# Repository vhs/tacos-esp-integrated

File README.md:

# TACOS ESP integrated

This is the integrated interlock and terminal TACOS reference implementation on ESP/embedded (Platform IO).

## TACOS

[TACOS](https://github.com/vhs/tacos/) is an integrated tool access control operations system.

## Usage

* Clone this repository: `git clone https://github.com/vhs/tacos-esp-integrated`
* Copy includes/config.sample.h to includes/config.h
  * Configure NODE_ID
  * Enable and/or disable LOCKOUT and/or AUTH_TERMINAL functionality
  * Configure wifi, NODE_SECRET, backend, NTP, IO and default settings as needed
    * NODE_SECRET is only needed for authentication
* Copy `platformio.sample.ini` to `platformio.ini`
* Configure boards as needed
* Compile and upload

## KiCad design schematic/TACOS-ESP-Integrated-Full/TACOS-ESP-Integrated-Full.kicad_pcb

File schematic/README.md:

# Schematics

## TACOS-ESP-Integrated-Full

This is a schematic for the full TACOS-ESP-Integrated design, which includes arming and NFC functionality.

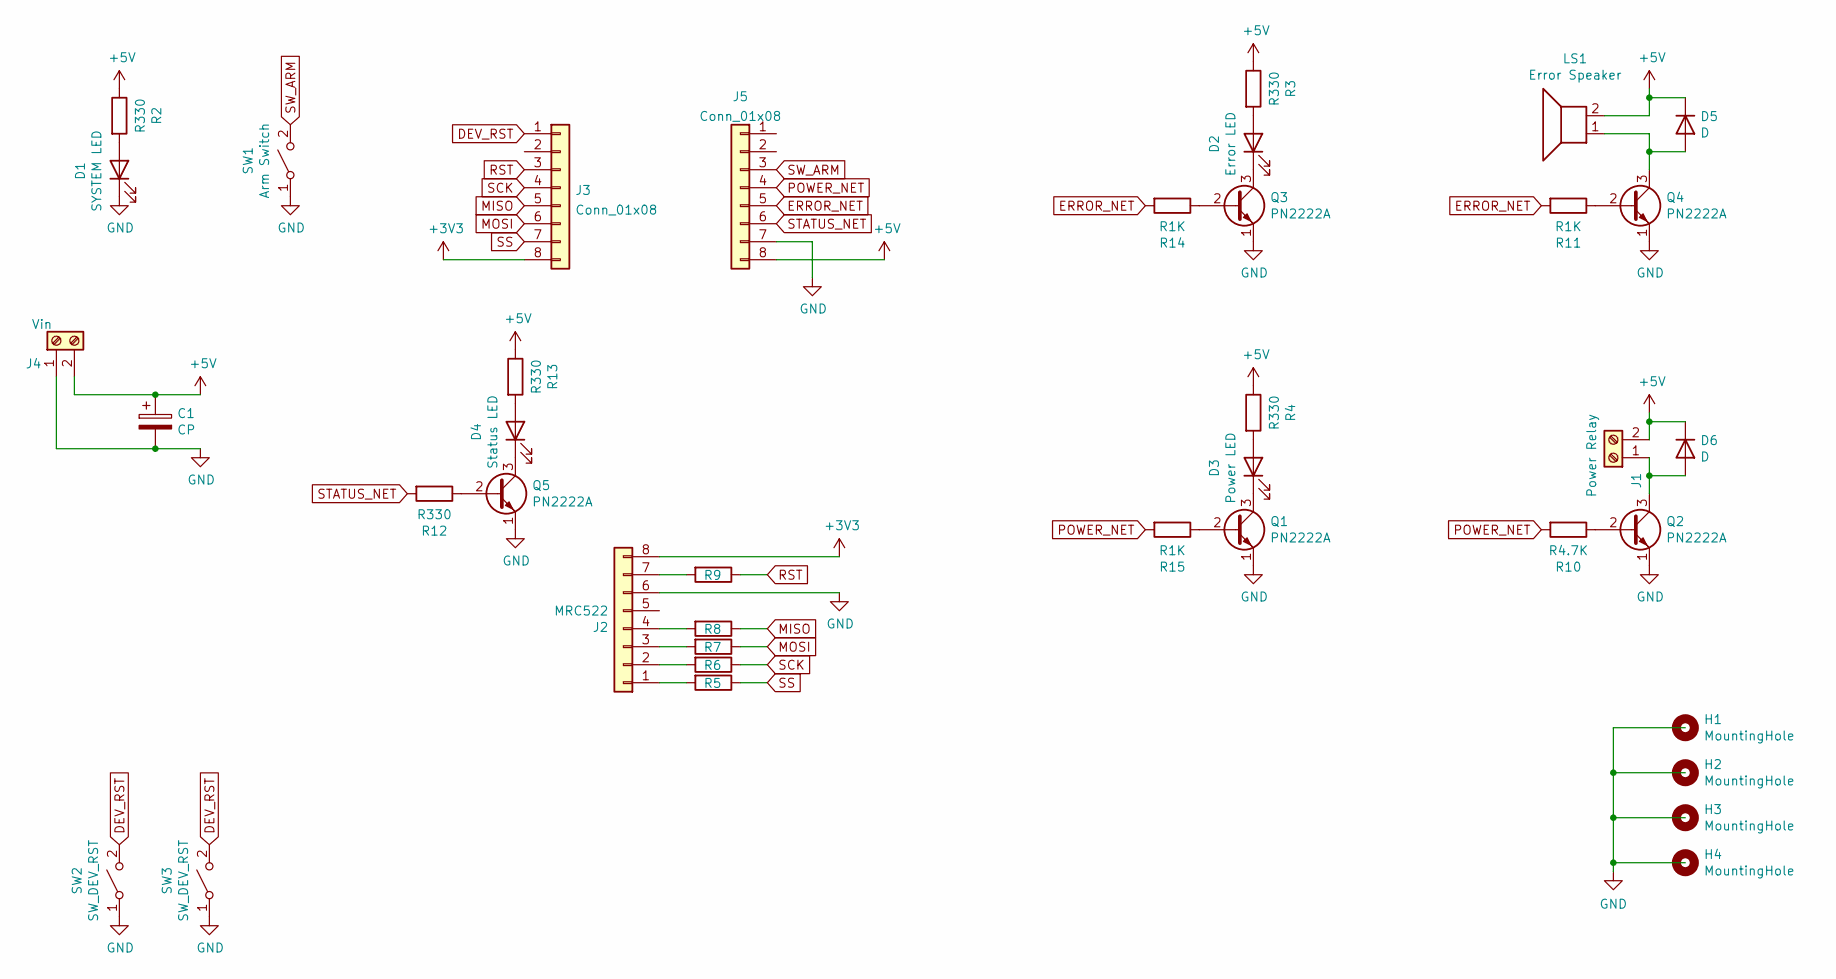
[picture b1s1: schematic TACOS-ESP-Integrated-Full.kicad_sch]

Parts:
C1: CP; CP_Radial_D5.0mm_P2.50mm
D1: SYSTEM LED; TerminalBlock_bornier-2_P5.08mm
D2: Error LED; TerminalBlock_bornier-2_P5.08mm
D3: Power LED; TerminalBlock_bornier-2_P5.08mm
D4: Status LED; TerminalBlock_bornier-2_P5.08mm
D5, D6: D; D_0603_1608Metric
H1, H2, H3, H4: MountingHole; MountingHole_3.2mm_M3_Pad
J1: Power Relay; TerminalBlock_bornier-2_P5.08mm
J2: MRC522; PinHeader_1x08_P2.54mm_Vertical
J3, J5: Conn_01x08; PinSocket_1x08_P2.54mm_Vertical
J4: Vin; TerminalBlock_bornier-2_P5.08mm
LS1: Error Speaker; TerminalBlock_bornier-2_P5.08mm
Q1, Q2, Q3, Q4, Q5: PN2222A; TO-92_Inline
R2, R3, R4, R12, R13: R330; R_0603_1608Metric
R5, R6, R7, R8, R9: R100; R_0603_1608Metric
R10: R4.7K; R_0603_1608Metric
R11, R14, R15: R1K; R_0603_1608Metric
SW1: Arm Switch; TerminalBlock_bornier-2_P5.08mm
SW2: SW_DEV_RST; TerminalBlock_bornier-2_P5.08mm
SW3: SW_DEV_RST; SW_SPST_PTS645

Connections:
+3V3: J2.8, J3.8
+5V: C1.1, D5.1 (K), D6.1 (K), J1.2, J4.2, J5.8, LS1.2, R2.1, R3.1, R4.1, R13.1
DEV_RST: J3.1, SW2.2 (B), SW3.2 (B)
ERROR_NET: J5.5, R11.2, R14.2
GND: C1.2, D1.1 (K), J2.6, J4.1, J5.7, Q1.1 (E), Q2.1 (E), Q3.1 (E), Q4.1 (E), Q5.1 (E), SW1.1 (A), SW2.1 (A), SW3.1 (A)
MISO: J3.5, R8.1
MOSI: J3.6, R7.1
unnamed: D1.2 (A), R2.2
unnamed: D2.2 (A), R3.2
unnamed: D2.1 (K), Q3.3 (C)
unnamed: D3.2 (A), R4.2
unnamed: D3.1 (K), Q1.3 (C)
unnamed: D4.2 (A), R13.2
unnamed: D4.1 (K), Q5.3 (C)
unnamed: D5.2 (A), LS1.1, Q4.3 (C)
unnamed: D6.2 (A), J1.1, Q2.3 (C)
unnamed: J2.1, R5.2
unnamed: J2.2, R6.2
unnamed: J2.3, R7.2
unnamed: J2.4, R8.2
unnamed: J2.7, R9.2
unnamed: Q1.2 (B), R15.1
unnamed: Q2.2 (B), R10.1
unnamed: Q3.2 (B), R14.1
unnamed: Q4.2 (B), R11.1
unnamed: Q5.2 (B), R12.1
POWER_NET: J5.4, R10.2, R15.2
RST: J3.3, R9.1
SCK: J3.4, R6.1
SS: J3.7, R5.1
STATUS_NET: J5.6, R12.2
SW_ARM: J5.3, SW1.2 (B)

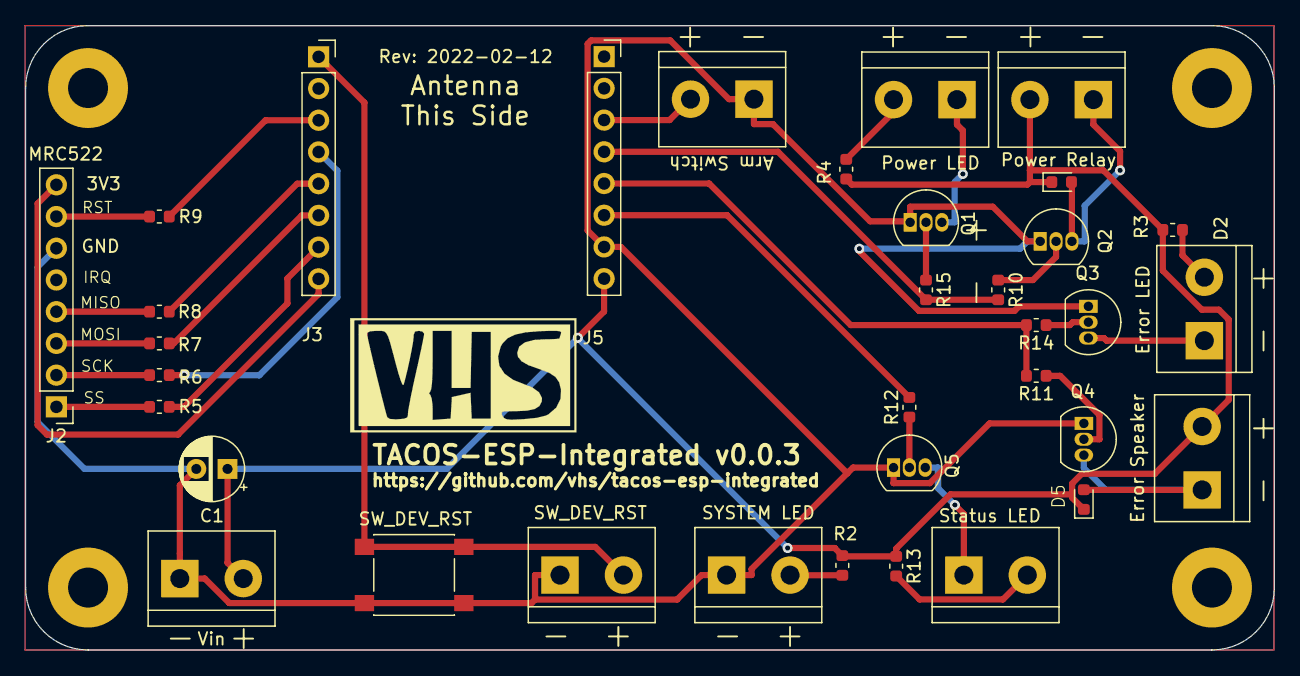
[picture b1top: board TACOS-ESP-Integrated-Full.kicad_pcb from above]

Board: 2 copper layers, 100.0 x 50.0 mm, 39 parts (0 on the bottom side), 32 nets.

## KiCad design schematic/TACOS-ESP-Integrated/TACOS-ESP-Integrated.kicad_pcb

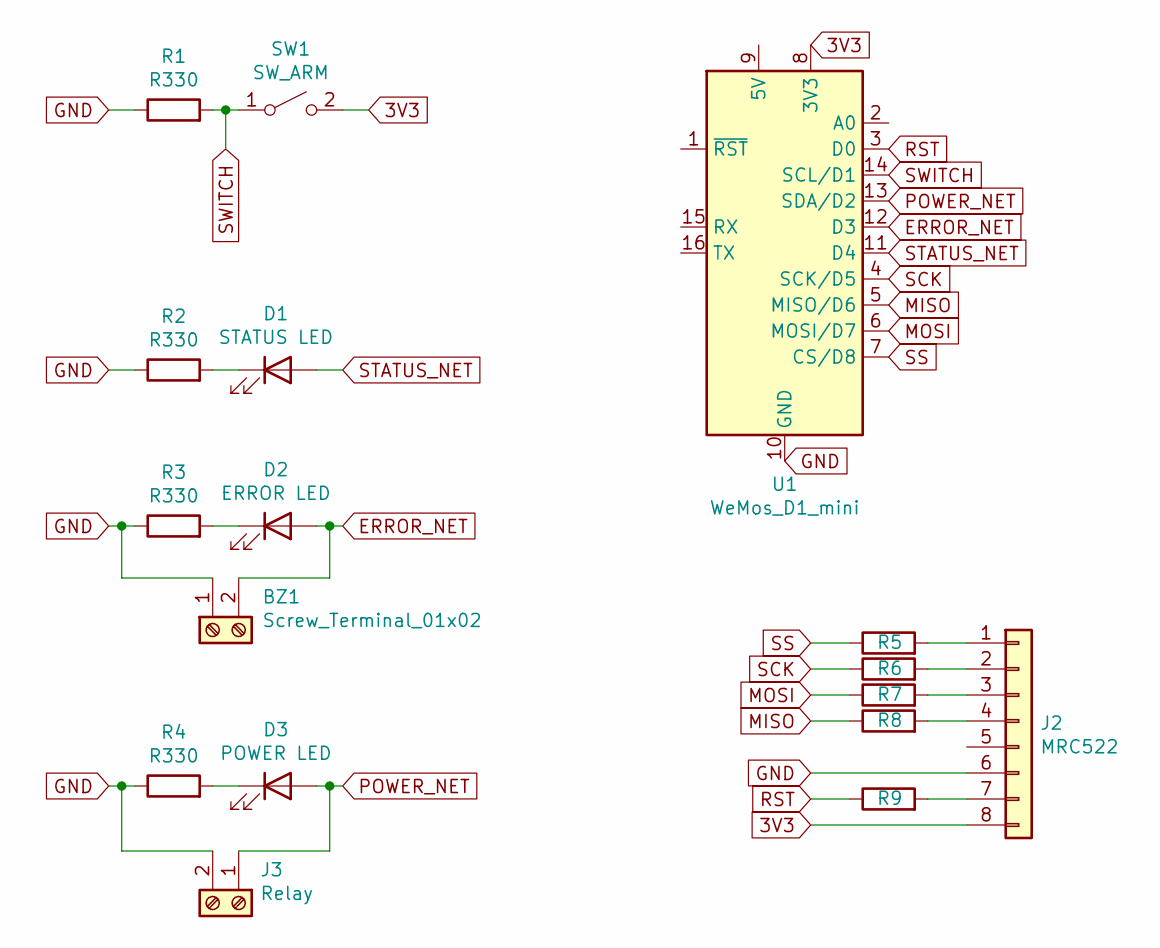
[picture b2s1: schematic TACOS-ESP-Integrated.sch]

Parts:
BZ1: Screw_Terminal_01x02; TerminalBlock_bornier-2_P5.08mm
D1: STATUS LED; TerminalBlock_bornier-2_P5.08mm
D2: ERROR LED; TerminalBlock_bornier-2_P5.08mm
D3: POWER LED; TerminalBlock_bornier-2_P5.08mm
J2: MRC522; PinHeader_1x08_P2.54mm_Vertical
J3: Relay; TerminalBlock_bornier-2_P5.08mm
R1, R2, R3, R4: R330; R_0603_1608Metric
R5, R6, R7, R8, R9: R100; R_0603_1608Metric
SW1: SW_ARM; TerminalBlock_bornier-2_P5.08mm
U1: WeMos_D1_mini; WEMOS_D1_mini_light

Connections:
3V3: J2.8, SW1.2 (B), U1.8 (3V3)
ERROR_NET: BZ1.2, D2.2 (A), U1.12 (D3)
GND: BZ1.1, J2.6, J3.2, R1.1, R2.1, R3.1, R4.1, U1.10 (GND)
MISO: R8.1, U1.5 (MISO/D6)
MOSI: R7.1, U1.6 (MOSI/D7)
unnamed: D1.1 (K), R2.2
unnamed: D2.1 (K), R3.2
unnamed: D3.1 (K), R4.2
unnamed: J2.1, R5.2
unnamed: J2.2, R6.2
unnamed: J2.3, R7.2
unnamed: J2.4, R8.2
unnamed: J2.7, R9.2
POWER_NET: D3.2 (A), J3.1, U1.13 (SDA/D2)
RST: R9.1, U1.3 (D0)
SCK: R6.1, U1.4 (SCK/D5)
SS: R5.1, U1.7 (CS/D8)
STATUS_NET: D1.2 (A), U1.11 (D4)
SWITCH: R1.2, SW1.1 (A), U1.14 (SCL/D1)

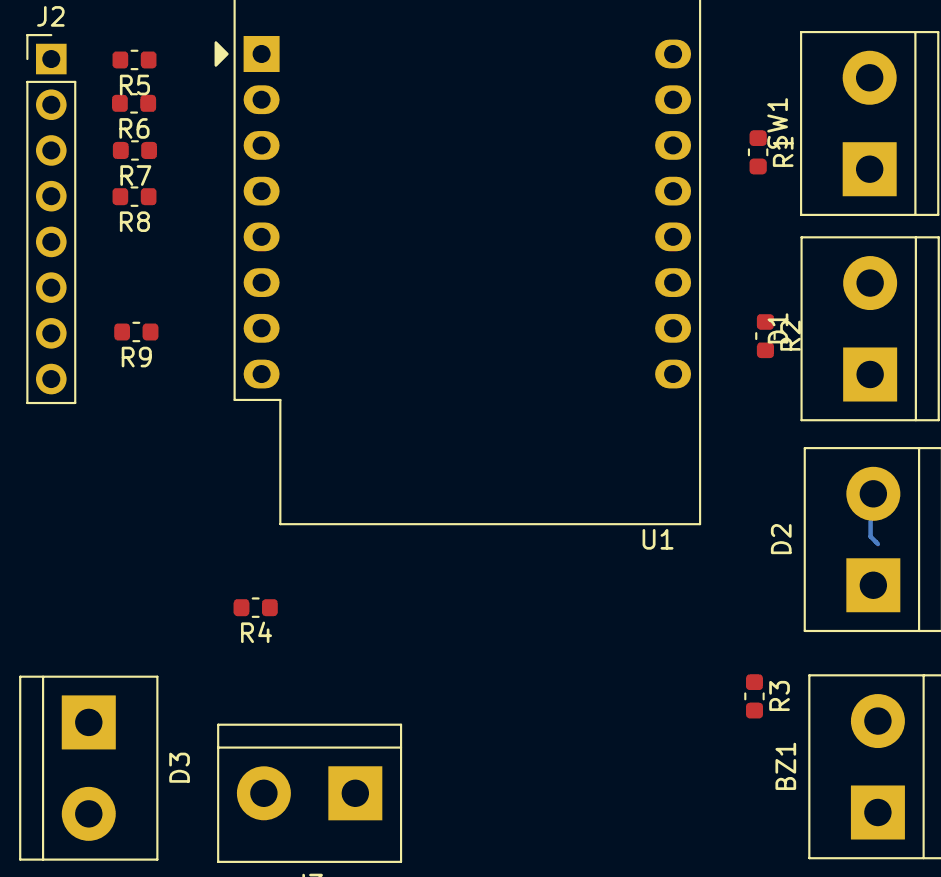
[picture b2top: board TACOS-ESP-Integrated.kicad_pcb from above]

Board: 2 copper layers, 17 parts (0 on the bottom side), 19 nets.

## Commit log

2020-09-25 New initial working version
2021-01-19 Schematic WIP
2021-01-19 Removed DSN file
2021-01-20 Schematic updates
2022-02-07 cert-auth-cert: updated LetsEncrypt root certificate
2022-02-07 Various: cleaned up/improved power states - also aligned server armed state data
2022-02-08 schematic: fully integrated with NFC
2022-02-09 schematic/README: initial version
2022-02-09 schematic: update
2022-02-11 Internal pull-up support for the button
2022-02-11 Improved internal pull-up button input support
2022-02-11 Default internal pull-up button input support
2022-02-11 Various: improved state handling
2022-02-11 schematic: update - default to pulldown circuit
2022-02-11 config.lolin-d1-mini.h: improved sample config
2022-02-11 Default internal pull-up button input
2022-02-12 schematic: update - routed
2022-02-12 schematic: updates
2022-02-13 schematic: updates - redid routing - redid logo
2022-02-13 Release v0.0.2
2024-11-05 feat(board): 2024 updates
